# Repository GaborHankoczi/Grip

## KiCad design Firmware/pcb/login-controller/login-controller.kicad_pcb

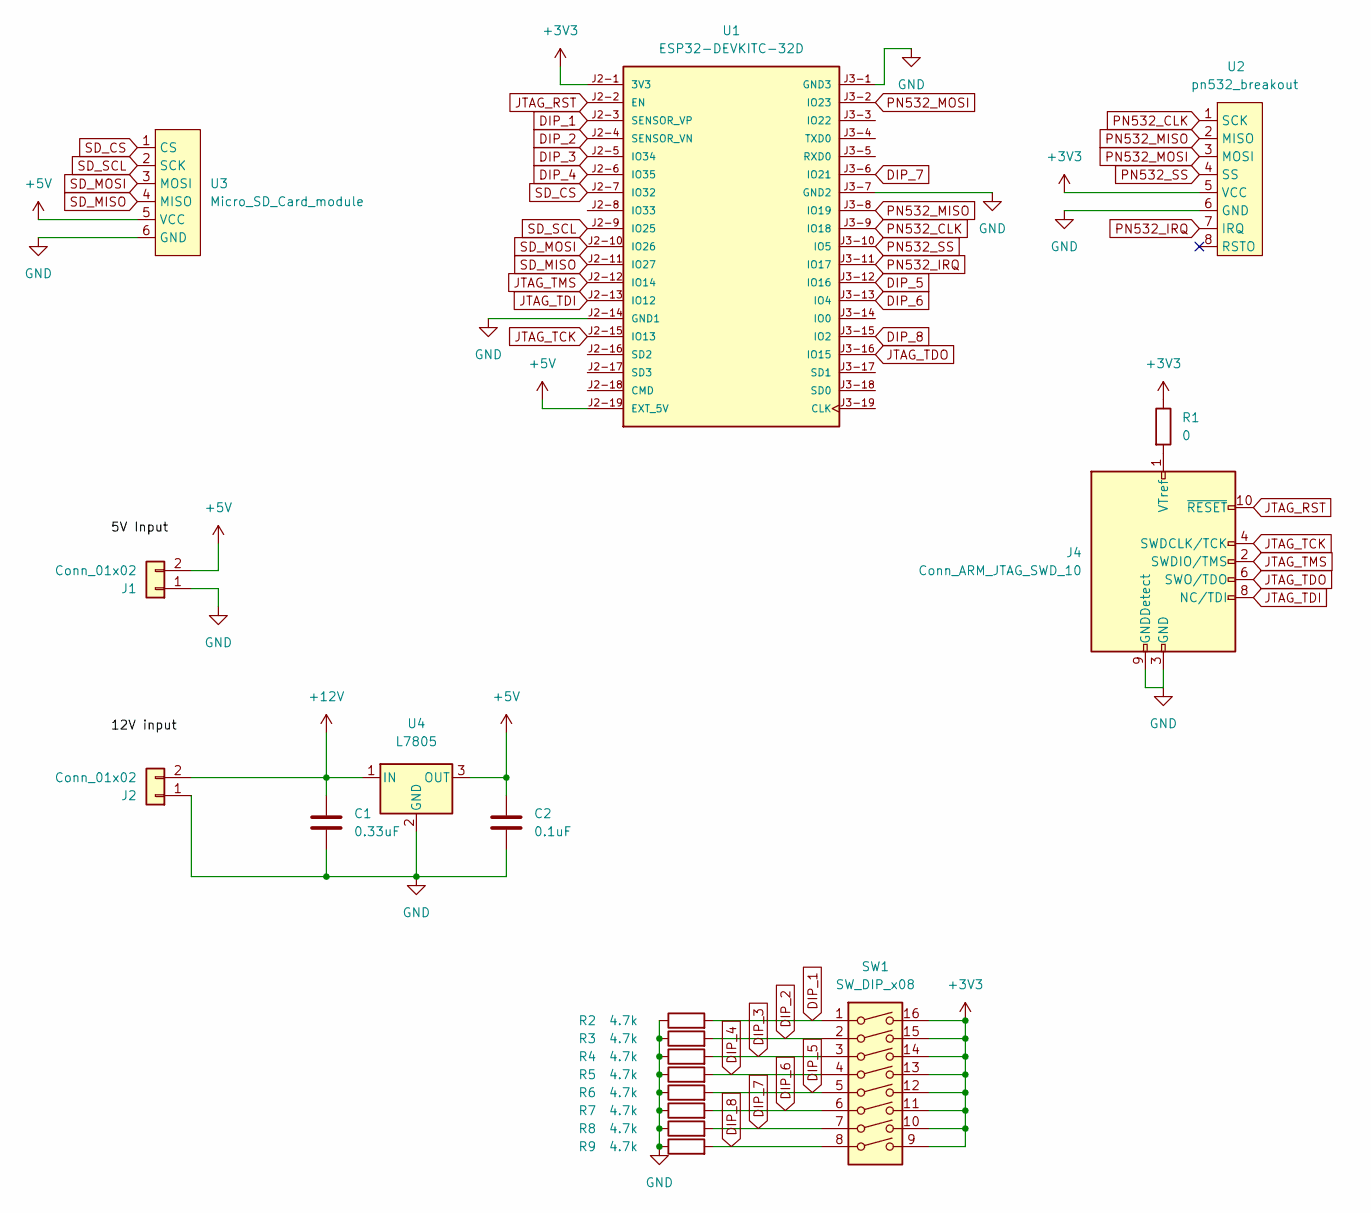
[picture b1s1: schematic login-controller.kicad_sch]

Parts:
C1: 0.33uF; CP_Radial_Tantal_D5.5mm_P5.00mm
C2: 0.1uF; CP_Radial_Tantal_D5.5mm_P5.00mm
J1, J2: Conn_01x02; TerminalBlock_bornier-2_P5.08mm
J4: Conn_ARM_JTAG_SWD_10; PinHeader_2x10_P2.54mm_Vertical
R1: 0; R_0805_2012Metric
R2, R3, R4, R5, R6, R7, R8, R9: 4.7k; R_1206_3216Metric_Pad1.30x1.75mm_HandSolder
SW1: SW_DIP_x08; SW_DIP_SPSTx08_Slide_9.78x22.5mm_W7.62mm_P2.54mm
U1: ESP32-DEVKITC-32D; MODULE_ESP32-DEVKITC-32D; PARTREV V4
U2: pn532_breakout
U3: Micro_SD_Card_module; SD_Card_Module
U4: L7805; PinSocket_1x03_P2.54mm_Vertical

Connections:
+3V3: R1.1, SW1.9, SW1.10, SW1.11, SW1.12, SW1.13, SW1.14, SW1.15, SW1.16, U1.J2-1 (3V3), U2.5 (VCC)
+5V: C2.1, J1.2, U1.J2-19 (EXT_5V), U3.5 (VCC), U4.3 (OUT)
+12V: C1.1, J2.2, U4.1 (IN)
DIP_1: R2.2, SW1.1, U1.J2-3 (SENSOR_VP)
DIP_2: R3.2, SW1.2, U1.J2-4 (SENSOR_VN)
DIP_3: R4.2, SW1.3, U1.J2-5 (IO34)
DIP_4: R5.2, SW1.4, U1.J2-6 (IO35)
DIP_5: R6.2, SW1.5, U1.J3-12 (IO16)
DIP_6: R7.2, SW1.6, U1.J3-13 (IO4)
DIP_7: R8.2, SW1.7, U1.J3-6 (IO21)
DIP_8: R9.2, SW1.8, U1.J3-15 (IO2)
GND: C1.2, C2.2, J1.1, J2.1, J4.3 (GND), J4.5 (GND), J4.9 (GNDDetect), R2.1, R3.1, R4.1, R5.1, R6.1, R7.1, R8.1, R9.1, U1.J2-14 (GND1), U1.J3-1 (GND3), U1.J3-7 (GND2), U2.6 (GND), U3.6 (GND), U4.2 (GND)
JTAG_RST: J4.10 (~RESET), U1.J2-2 (EN)
JTAG_TCK: J4.4 (SWDCLK/TCK), U1.J2-15 (IO13)
JTAG_TDI: J4.8 (NC/TDI), U1.J2-13 (IO12)
JTAG_TDO: J4.6 (SWO/TDO), U1.J3-16 (IO15)
JTAG_TMS: J4.2 (SWDIO/TMS), U1.J2-12 (IO14)
unnamed: J4.1 (VTref), R1.2
PN532_CLK: U1.J3-9 (IO18), U2.1 (SCK)
PN532_IRQ: U1.J3-11 (IO17), U2.7 (IRQ)
PN532_MISO: U1.J3-8 (IO19), U2.2 (MISO)
PN532_MOSI: U1.J3-2 (IO23), U2.3 (MOSI)
PN532_SS: U1.J3-10 (IO5), U2.4 (SS)
SD_CS: U1.J2-7 (IO32), U3.1 (CS)
SD_MISO: U1.J2-11 (IO27), U3.4 (MISO)
SD_MOSI: U1.J2-10 (IO26), U3.3 (MOSI)
SD_SCL: U1.J2-9 (IO25), U3.2 (SCK)

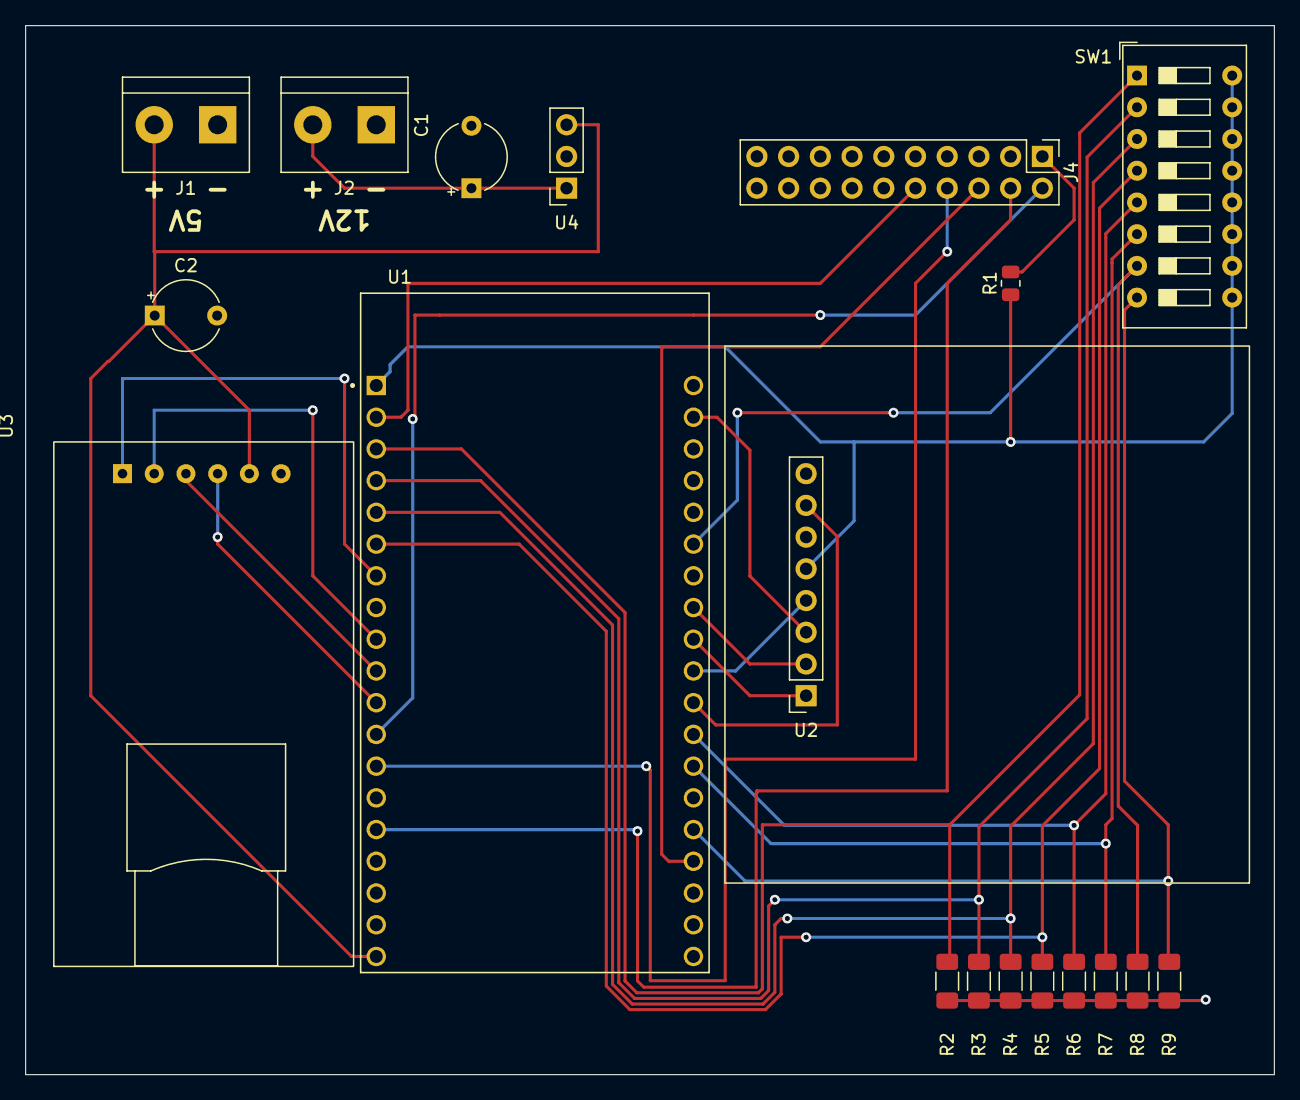
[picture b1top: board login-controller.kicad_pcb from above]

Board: 2 copper layers, 100.0 x 84.0 mm, 19 parts (0 on the bottom side), 27 nets.

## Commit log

2023-03-08 gitignores added
2023-03-15 Server initial commit
2023-03-17 Complete user endpoint
2023-03-21 Created welcome Activity
    Created the welcome Activity and configured the splash screen and app icon.
2023-03-23 Created new Activities
    Created the Login, Register and ForgotPassword Activities.
2023-03-26 Server Dockerfile added, TestEnvironment added
2023-03-27 EmailService created with external provider
2023-03-29 Firmware: New library included
2023-03-29 Firmware: added documentation, working reading tags
2023-03-29 Firmware: better working nfc
2023-03-29 Added navigation between pages
2023-03-30 Added login functionality
2023-03-30 Server: Attendance basics
2023-04-02 Firmware: better nfc debugging
2023-04-02 Proper driver usage
2023-04-04 Removed the register option and added validation to the login process
2023-04-06 Firmware: NDEF messages implemented
2023-04-06 Implemented the confirm email process
    Implemented the confirm email process, added new models, and commented several classes.
2023-04-07 Firmware: Added IRQ line to communication
2023-04-07 Firmware: Sometimes working card emulation
2023-04-07 Firmware: Working NFC Emulation Reading and writing
2023-04-10 Implemented the logic and view behind the forgot password process.
    Implemented the logic and view behind the forgot password process and commented every important class, method and property.
2023-04-16 Server: Database updated with classes, attendance, station secret key distribution implemented, emulated scan token verification implemented, dechunking and api key verification middlewares implement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
2023-04-19 PCB Created
2023-04-20 Firmware: DIP Switch added
2023-05-01 Class, Group, PassiveTag endpoints added
2023-05-01 Added Exempt endpoints and to the database
2023-05-01 Fix User Validator
2023-05-04 Server: Certificate loading is now configurable
2023-05-04 Temporary NFC solution
2023-05-04 Firmware: IO fix
2023-05-06 Server: Restructuring, refactoring, service abstraction implemented, some endpoins documented
2023-05-06 Server: Complete endpoint documentation
2023-05-07 Server: Dockerfile updated
2023-05-11 Complete NFC feature
2023-05-11 Mobile: Created gitignore file
2023-05-12 Server: added attendance by day endpoint and implementation
2023-05-12 Server: ProblemDetails and Middleware FIx
2023-05-12 Server: Added Exempt implementation to GetAttendanceForDay
2023-05-13 Server: Providers refactored, Student endpoints added and implemented
2023-05-15 Server: Real time push notification for station scans, passive tag scan processing implemented
2023-05-16 Sever: Documentation
2023-05-21 Documentation and namespace fixes
2023-05-23 Firmware: documentation
2023-05-23 Server: Fixes
2023-05-23 Created a basic interface for admins, teachers and students
2023-05-24 Server DB fix
2023-05-24 Mobile gitignore added
2023-05-25 Mobile: List users for admins and teachers
2023-05-25 Mobile: Current classes and exempt pages
2023-05-27 Mobile: Create group, class, exempt. attendance implemented
2023-05-27 Mobile: Create group, class, exempt, attendance extra files
2023-05-27 Server: Exception descriptions and possible proxy configuration
2023-05-28 Mobile: Implemented UserDetailPopup
2023-06-20 Server: Http OPTIONS verb support
2023-06-21 Working OAuth2
2023-06-22 SignalR extended with initial send and IdentityServer compliant DB user identification
2023-06-22 Added sample IdentityServer signing key
2023-06-22 Added documentation
2023-06-22 Updated IdentityServer Config for different configurations
2023-06-26 Bemutatásra kész
2023-09-26 Everlink initial commit
2023-09-26 Everlink server implementation fix
2023-09-27 Everlink adapter: Persistent storage, logging added, dockerfile added
2023-09-27 gitignore file updated
2023-09-27 Log file format fixed
2023-10-15 Threaded keep alive
2023-10-15 Threaded keep alive fix
2023-10-15 Server: Everlink processing
2023-10-18 Adapter heartbeat integrated into main processing loop
2023-10-24 Added m2m client for everlink endpoints
